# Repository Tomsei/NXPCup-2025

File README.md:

# NXPCup-2025
Software und Hardware für den NXP-Cup 2025
- **Software Ordner:** gesamter erzeugter Quellcode
- **Hardware Ordner:** Dokumentation der gewählten Hardware mitsamt Recherche

# NXP Cup
Der [NXP-Cup](https://nxpcup.nxp.com/) ist ein Internationaler Wettbewerb, ausgerichtet vom Unternehmen NXP.
Es findet jährlich ein Rennen statt, bei dem die Modellfahrzeuge der jeweiligen Teilnehmer gegeneinander antreten. Um zu gewinnen muss das eigene Fahrzeug die unbekannte Rennstrecke in der schnellsten Geschwindigkeit abfahren und zusätzlich noch mit Präzision vor einem Hindernis zum stehen kommen.

# Styleguides
### Code
- Sprache (Variablen, Funktionen): Englisch
- Kommentare: Englisch
- Schreibweise: 
    - CamelCase
    - Funktionen / Variablen: starten klein
    - Typ-Klasse: starten groß
    - Variablen:
        - Boolen: Präfix is (isValid)
        - constant: konsequent großschreiben von CONSTANT
    - Leerzeichen zwischen Operatoren:  
    ```x + y``` anstatt ```a+y```; ```[x, y]``` anstatt ```[x,y]```
    - Klammerung: Klammer in gleicher Zeile dahinter
        ```
        function () {
            ...
        }
        ```
  - #defines werden komplett groß geschrieben ```#define NEW_DEFINE_VALUE```
### GIT
- Commits: Englisch
- Dateien: Englisch ```exmpleFileForDemonstration``` 
    - Der Name von Komponenten wird wenn notwendig mit _KOMPONENTENNAME an Datei angehangen
- Verzeichnisse: Englisch
- Wiki: Deutsch
- Issues: Deutsch

<br>
<br>

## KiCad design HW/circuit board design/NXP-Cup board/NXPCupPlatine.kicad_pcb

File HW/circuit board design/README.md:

# Platinenentwicklung

Hier werden die für die Platinen relevanten Dateien gespeichert. (Gerber sowie Projektdateien und Dokumentation)

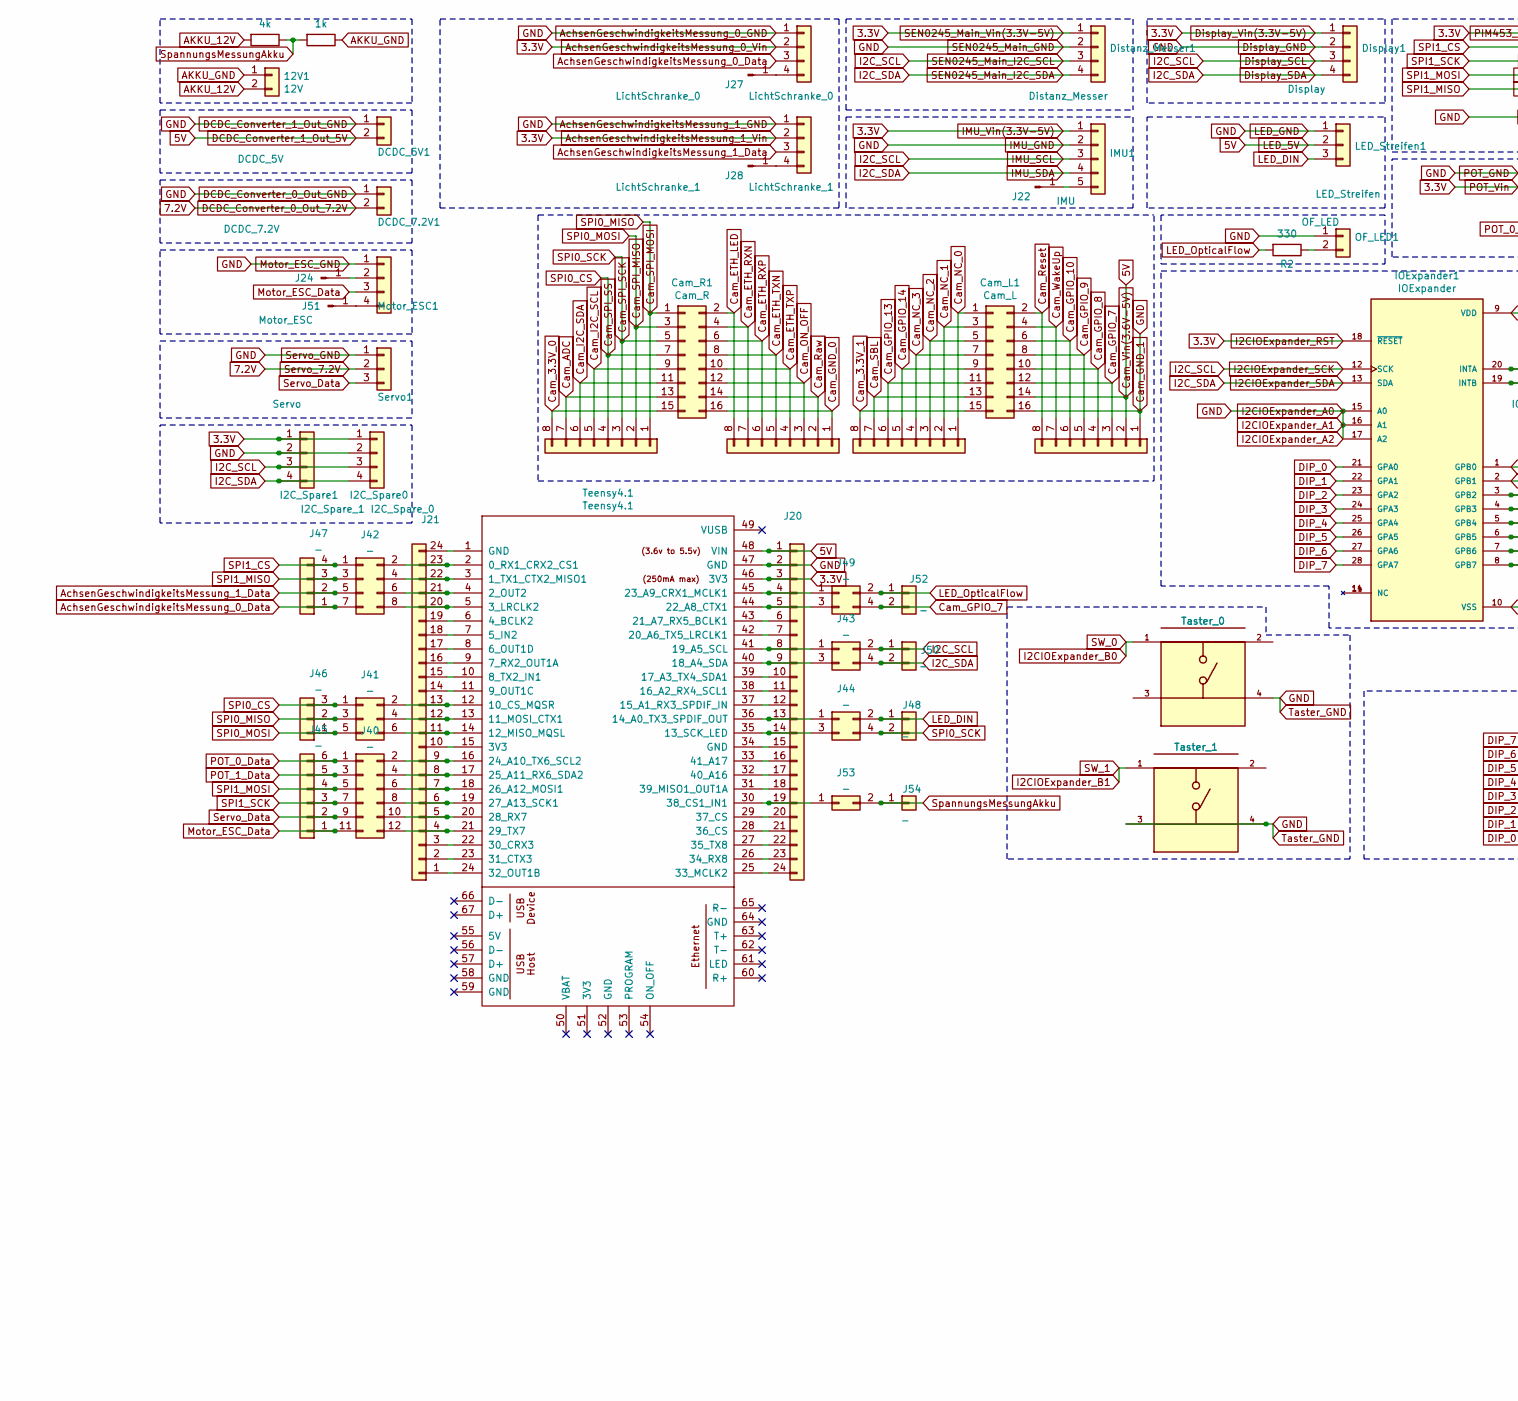
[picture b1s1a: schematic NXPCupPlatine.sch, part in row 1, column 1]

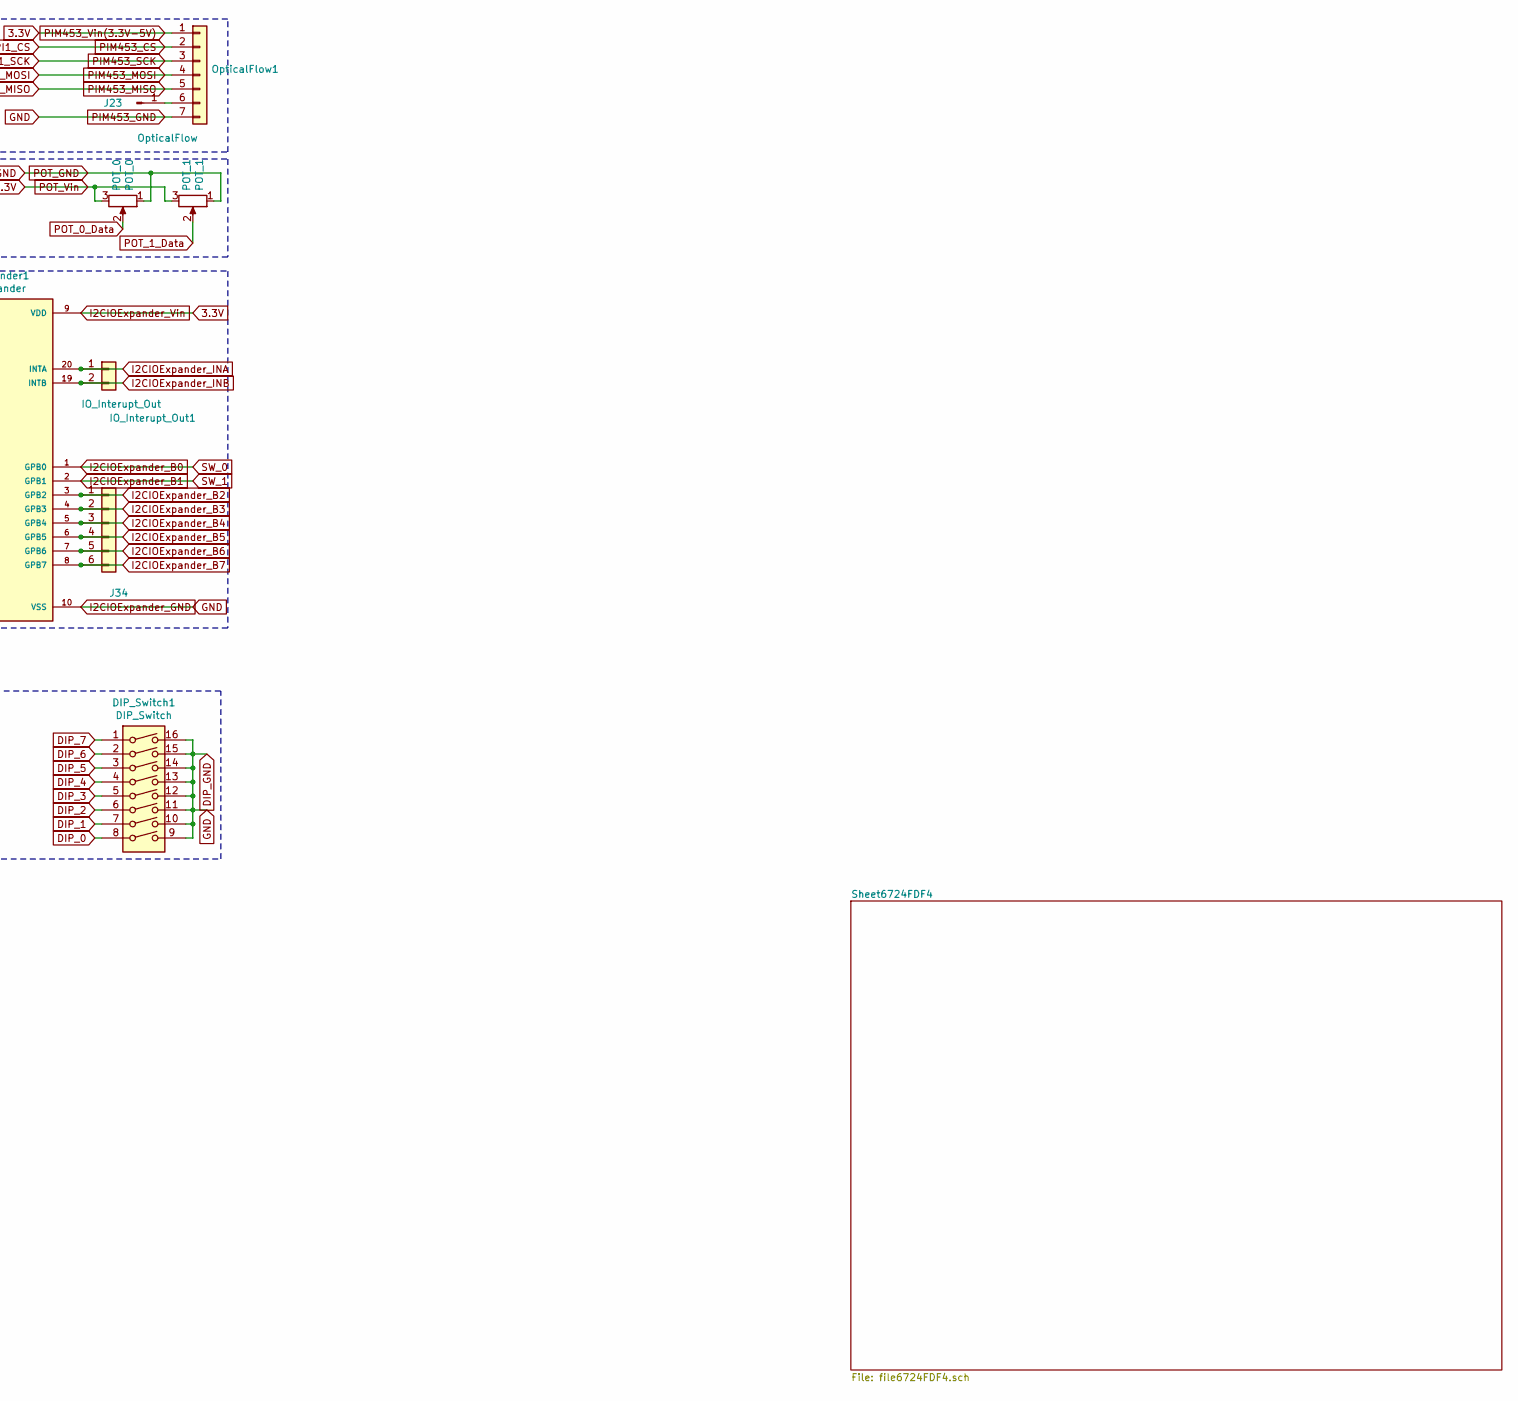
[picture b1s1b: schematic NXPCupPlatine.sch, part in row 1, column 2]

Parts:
12V1: 12V; PinHeader_1x02_P2.54mm_Vertical
Cam_L1: Cam_L; PinHeader_2x08_P2.54mm_Vertical
Cam_R1: Cam_R; PinHeader_2x08_P2.54mm_Vertical
DCDC_5V1: DCDC_5V; PhoenixContact_MSTBA_2,5_2-G_1x02_P5.00mm_Horizontal
DCDC_7.2V1: DCDC_7.2V; PhoenixContact_MSTBA_2,5_2-G_1x02_P5.00mm_Horizontal
DIP_Switch1: DIP_Switch; DIP-16_W7.62mm_LongPads
Display1: Display; PinSocket_1x04_P2.54mm_Vertical
Distanz_Messer1: Distanz_Messer; PinHeader_1x04_P2.54mm_Vertical
I2C_Spare_0: I2C_Spare0; PinHeader_1x04_P2.54mm_Vertical
I2C_Spare_1: I2C_Spare1; PinHeader_1x04_P2.54mm_Vertical
IMU1: IMU; PinHeader_1x05_P2.54mm_Vertical
IOExpander1: IOExpander; DIP787W45P254L3556H508Q28; PARTREV D
IO_Interupt_Out1: IO_Interupt_Out; PinSocket_1x02_P2.54mm_Vertical
J5, J7, J8, J10: PinHeader_1x08_P2.54mm_Vertical
J20, J21: PinHeader_1x24_P2.54mm_Vertical
J22, J23, J24, J27, J28, J51: PinHeader_1x01_P2.54mm_Vertical
J34: PinSocket_1x06_P2.54mm_Vertical
J40: _; PinHeader_2x06_P2.54mm_Vertical
J41: _; PinHeader_2x03_P2.54mm_Vertical
J42: _; PinHeader_2x04_P2.54mm_Vertical
J43, J44, J49: _; PinHeader_2x02_P2.54mm_Vertical
J45: _; PinHeader_1x06_P2.54mm_Vertical
J46: _; PinHeader_1x03_P2.54mm_Vertical
J47: _; PinHeader_1x04_P2.54mm_Vertical
J48, J50, J52: _; PinHeader_1x02_P2.54mm_Vertical
J53: _; PinHeader_2x01_P2.54mm_Vertical
J54: _; PinHeader_1x01_P2.54mm_Vertical
LED_Streifen1: LED_Streifen; PinSocket_1x03_P2.54mm_Vertical
LichtSchranke_0: LichtSchranke_0; PinSocket_1x04_P2.54mm_Vertical
LichtSchranke_1: LichtSchranke_1; PinSocket_1x04_P2.54mm_Vertical
Motor_ESC1: Motor_ESC; PinHeader_1x04_P2.54mm_Vertical
OF_LED1: OF_LED; PinSocket_1x02_P2.54mm_Vertical
OpticalFlow1: OpticalFlow; PinHeader_1x07_P2.54mm_Vertical
POT_0: POT_0; Potentiometer_Alpha_RD901F-40-00D_Single_Vertical
POT_1: POT_1; Potentiometer_Alpha_RD901F-40-00D_Single_Vertical
R0: 4k; R_Axial_DIN0204_L3.6mm_D1.6mm_P1.90mm_Vertical
R1: 1k; R_Axial_DIN0204_L3.6mm_D1.6mm_P1.90mm_Vertical
R2: 330; R_Axial_DIN0204_L3.6mm_D1.6mm_P1.90mm_Vertical
Servo1: Servo; PinHeader_1x03_P2.54mm_Vertical
Taster_0: Taster_0; SW_TS02-66-95-BK-260-LCR-D; PARTREV 1.0
Taster_1: Taster_1; SW_TS02-66-95-BK-260-LCR-D; PARTREV 1.0
Teensy4.1: Teensy4.1; Teensy41

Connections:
3.3V: Display1.1, Distanz_Messer1.1, I2C_Spare_0.1, I2C_Spare_1.1, IMU1.1, IOExpander1.9 (VDD), IOExpander1.18 (~RESET), J20.3, LichtSchranke_0.2, LichtSchranke_1.2, OpticalFlow1.1, POT_0.3, POT_1.3, Teensy4.1.46 (3V3)
5V: Cam_L1.14, DCDC_5V1.2, J10.2, J20.1, LED_Streifen1.2, Teensy4.1.48 (VIN)
7.2V: DCDC_7.2V1.2, Servo1.2
AKKU_12V: 12V1.2, R0.2
AKKU_GND: 12V1.1, R1.1
AchsenGeschwindigkeitsMessung_0_Data: J42.7, J47.1, LichtSchranke_0.3
AchsenGeschwindigkeitsMessung_0_GND: Cam_L1.16, DCDC_5V1.1, DCDC_7.2V1.1, DIP_Switch1.9, DIP_Switch1.10, DIP_Switch1.11, DIP_Switch1.12, DIP_Switch1.13, DIP_Switch1.14, DIP_Switch1.15, DIP_Switch1.16, Display1.2, Distanz_Messer1.2, I2C_Spare_0.2, I2C_Spare_1.2, IMU1.2, IOExpander1.10 (VSS), IOExpander1.15 (A0), IOExpander1.16 (A1), IOExpander1.17 (A2), J10.1, J20.2, LED_Streifen1.1, LichtSchranke_0.1, LichtSchranke_1.1, Motor_ESC1.1, OF_LED1.1, OpticalFlow1.7, POT_0.1, POT_1.1, Servo1.1, Taster_0.4, Taster_1.3, Taster_1.4, Teensy4.1.47 (GND)
AchsenGeschwindigkeitsMessung_1_Data: J42.5, J47.2, LichtSchranke_1.3
Cam_3.3V_0: Cam_R1.15, J5.8
Cam_3.3V_1: Cam_L1.15, J8.8
Cam_ADC: Cam_R1.13, J5.7
Cam_ETH_LED: Cam_R1.2, J7.8
Cam_ETH_RXN: Cam_R1.4, J7.7
Cam_ETH_RXP: Cam_R1.6, J7.6
Cam_ETH_TXN: Cam_R1.8, J7.5
Cam_ETH_TXP: Cam_R1.10, J7.4
Cam_GND_0: Cam_R1.16, J7.1
Cam_GPIO_7: Cam_L1.12, J10.3, J49.4, J52.2
Cam_GPIO_8: Cam_L1.10, J10.4
Cam_GPIO_9: Cam_L1.8, J10.5
Cam_GPIO_10: Cam_L1.6, J10.6
Cam_GPIO_13: Cam_L1.11, J8.6
Cam_GPIO_14: Cam_L1.9, J8.5
Cam_I2C_SCL: Cam_R1.9, J5.5
Cam_I2C_SDA: Cam_R1.11, J5.6
Cam_NC_0: Cam_L1.1, J8.1
Cam_NC_1: Cam_L1.3, J8.2
Cam_NC_2: Cam_L1.5, J8.3
Cam_NC_3: Cam_L1.7, J8.4
Cam_ON_OFF: Cam_R1.12, J7.3
Cam_Raw: Cam_R1.14, J7.2
Cam_Reset: Cam_L1.2, J10.8
Cam_SBL: Cam_L1.13, J8.7
Cam_SPI_MISO: Cam_R1.3, J5.2, J41.5, J46.1
Cam_SPI_MOSI: Cam_R1.1, J5.1, J41.3, J46.2
Cam_SPI_SCK: Cam_R1.5, J5.3, J44.4, J48.2
Cam_SPI_SS: Cam_R1.7, J5.4, J41.1, J46.3
Cam_WakeUp: Cam_L1.4, J10.7
DIP_0: DIP_Switch1.8, IOExpander1.21 (GPA0)
DIP_1: DIP_Switch1.7, IOExpander1.22 (GPA1)
DIP_2: DIP_Switch1.6, IOExpander1.23 (GPA2)
DIP_3: DIP_Switch1.5, IOExpander1.24 (GPA3)
DIP_4: DIP_Switch1.4, IOExpander1.25 (GPA4)
DIP_5: DIP_Switch1.3, IOExpander1.26 (GPA5)
DIP_6: DIP_Switch1.2, IOExpander1.27 (GPA6)
DIP_7: DIP_Switch1.1, IOExpander1.28 (GPA7)
Display_SCL: Display1.3, Distanz_Messer1.3, I2C_Spare_0.3, I2C_Spare_1.3, IMU1.3, IOExpander1.12 (SCK), J43.2, J50.1
Display_SDA: Display1.4, Distanz_Messer1.4, I2C_Spare_0.4, I2C_Spare_1.4, IMU1.4, IOExpander1.13 (SDA), J43.4, J50.2
I2CIOExpander_B0: IOExpander1.1 (GPB0), Taster_0.1
I2CIOExpander_B1: IOExpander1.2 (GPB1), Taster_1.1
I2CIOExpander_B2: IOExpander1.3 (GPB2), J34.1
I2CIOExpander_B3: IOExpander1.4 (GPB3), J34.2
I2CIOExpander_B4: IOExpander1.5 (GPB4), J34.3
I2CIOExpander_B5: IOExpander1.6 (GPB5), J34.4
I2CIOExpander_B6: IOExpander1.7 (GPB6), J34.5
I2CIOExpander_B7: IOExpander1.8 (GPB7), J34.6
I2CIOExpander_INA: IOExpander1.20 (INTA), IO_Interupt_Out1.1
I2CIOExpander_INB: IOExpander1.19 (INTB), IO_Interupt_Out1.2
LED_DIN: J44.2, J48.1, LED_Streifen1.3
LED_OpticalFlow: J49.2, J52.1, R2.2
Motor_ESC_Data: J40.11, J45.1, Motor_ESC1.3
unnamed: IMU1.5, J22.1
unnamed: IOExpander1.11 (NC), IOExpander1.14 (NC)
unnamed: J20.4, J49.1, Teensy4.1.45 (23_A9_CRX1_MCLK1)
unnamed: J20.5, J49.3, Teensy4.1.44 (22_A8_CTX1)
unnamed: J20.6, Teensy4.1.43 (21_A7_RX5_BCLK1)
unnamed: J20.7, Teensy4.1.42 (20_A6_TX5_LRCLK1)
unnamed: J20.8, J43.1, Teensy4.1.41 (19_A5_SCL)
unnamed: J20.9, J43.3, Teensy4.1.40 (18_A4_SDA)
unnamed: J20.10, Teensy4.1.39 (17_A3_TX4_SDA1)
unnamed: J20.11, Teensy4.1.38 (16_A2_RX4_SCL1)
unnamed: J20.12, Teensy4.1.37 (15_A1_RX3_SPDIF_IN)
unnamed: J20.13, J44.1, Teensy4.1.36 (14_A0_TX3_SPDIF_OUT)
unnamed: J20.14, J44.3, Teensy4.1.35 (13_SCK_LED)
unnamed: J20.15, Teensy4.1.34 (GND)
unnamed: J20.16, Teensy4.1.33 (41_A17)
unnamed: J20.17, Teensy4.1.32 (40_A16)
unnamed: J20.18, Teensy4.1.31 (39_MISO1_OUT1A)
unnamed: J20.19, J53.1, Teensy4.1.30 (38_CS1_IN1)
unnamed: J20.20, Teensy4.1.29 (37_CS)
unnamed: J20.21, Teensy4.1.28 (36_CS)
unnamed: J20.22, Teensy4.1.27 (35_TX8)
unnamed: J20.23, Teensy4.1.26 (34_RX8)
unnamed: J20.24, Teensy4.1.25 (33_MCLK2)
unnamed: J21.1, Teensy4.1.24 (32_OUT1B)
unnamed: J21.2, Teensy4.1.23 (31_CTX3)
unnamed: J21.3, Teensy4.1.22 (30_CRX3)
unnamed: J21.4, J40.12, Teensy4.1.21 (29_TX7)
unnamed: J21.5, J40.10, Teensy4.1.20 (28_RX7)
unnamed: J21.6, J40.8, Teensy4.1.19 (27_A13_SCK1)
unnamed: J21.7, J40.6, Teensy4.1.18 (26_A12_MOSI1)
unnamed: J21.8, J40.4, Teensy4.1.17 (25_A11_RX6_SDA2)
unnamed: J21.9, J40.2, Teensy4.1.16 (24_A10_TX6_SCL2)
unnamed: J21.10, Teensy4.1.15 (3V3)
unnamed: J21.11, J41.6, Teensy4.1.14 (12_MISO_MQSL)
unnamed: J21.12, J41.4, Teensy4.1.13 (11_MOSI_CTX1)
unnamed: J21.13, J41.2, Teensy4.1.12 (10_CS_MQSR)
unnamed: J21.14, Teensy4.1.11 (9_OUT1C)
unnamed: J21.15, Teensy4.1.10 (8_TX2_IN1)
unnamed: J21.16, Teensy4.1.9 (7_RX2_OUT1A)
unnamed: J21.17, Teensy4.1.8 (6_OUT1D)
unnamed: J21.18, Teensy4.1.7 (5_IN2)
unnamed: J21.19, Teensy4.1.6 (4_BCLK2)
unnamed: J21.20, J42.8, Teensy4.1.5 (3_LRCLK2)
unnamed: J21.21, J42.6, Teensy4.1.4 (2_OUT2)
unnamed: J21.22, J42.4, Teensy4.1.3 (1_TX1_CTX2_MISO1)
unnamed: J21.23, J42.2, Teensy4.1.2 (0_RX1_CRX2_CS1)
unnamed: J21.24, Teensy4.1.1 (GND)
unnamed: J23.1, OpticalFlow1.6
unnamed: J24.1, Motor_ESC1.2
unnamed: J27.1, LichtSchranke_0.4
unnamed: J28.1, LichtSchranke_1.4
unnamed: J51.1, Motor_ESC1.4
unnamed: OF_LED1.2, R2.1
PIM453_CS: J42.1, J47.4, OpticalFlow1.2
PIM453_MISO: J42.3, J47.3, OpticalFlow1.5
PIM453_MOSI: J40.5, J45.4, OpticalFlow1.4
PIM453_SCK: J40.7, J45.3, OpticalFlow1.3
POT_0_Data: J40.1, J45.6, POT_0.2
POT_1_Data: J40.3, J45.5, POT_1.2
Servo_Data: J40.9, J45.2, Servo1.3
SpannungsMessungAkku: J53.2, J54.1, R0.1, R1.2

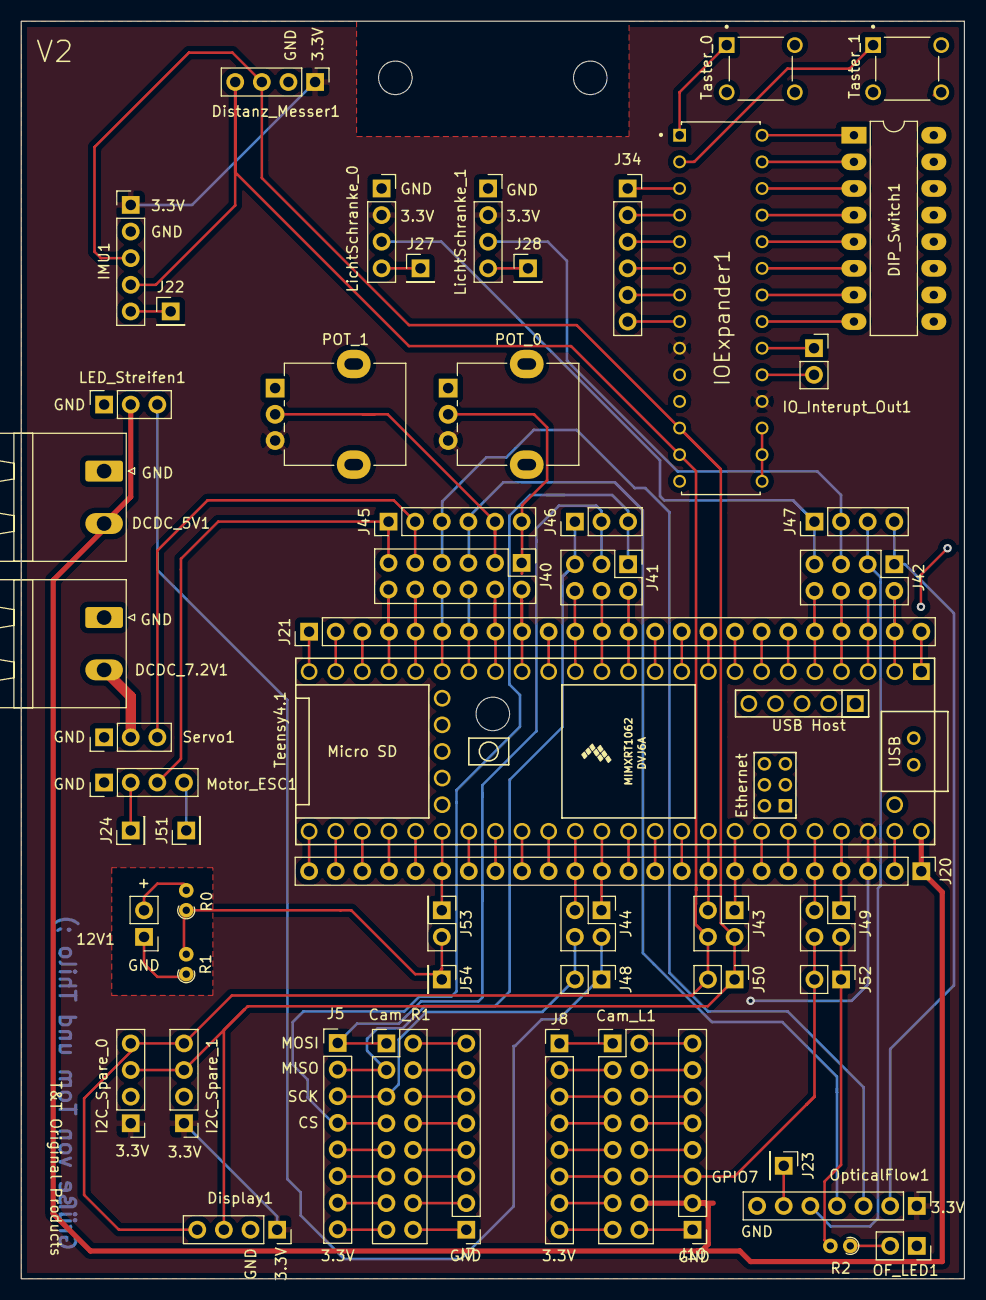
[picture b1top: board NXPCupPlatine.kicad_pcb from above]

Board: 2 copper layers, 90.0 x 120.0 mm, 55 parts (0 on the bottom side), 122 nets.

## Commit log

2024-07-11 initial structure
2024-07-18 add research structure
2024-07-18 complete research strucutre
2024-07-18 add more research results
2024-07-18 add first research results
2024-07-19 add styleguide
2024-07-21 add research results from 17.07
2024-07-23 add research results distance measurement
2024-07-23 add more research (distance measurement)
2024-07-23 add new research results
2024-07-24 add usecase + functional requirements
2024-07-25 rename directorys
2024-07-29 add some camera research
2024-08-01 some more research
2024-08-12 add new research (camera, display...)
2024-08-13 more processor research
2024-08-15 add processor resarch of (14.08)
2024-08-15 general structure
2024-08-16 clean up of research files
2024-08-16 update mikrocontroller research
2024-08-17 start defining Hardware-Kit (Teensy + Cam)
2024-08-19 add research results of 17.08
2024-08-19 add research results NXP-Gitbook
2024-08-20 new research (camera, car racing kit)
2024-08-21 first kit design
2024-08-21 add some changes to first kit
2024-08-24 update research results for kit
2024-08-26 update research (motor links)
2024-08-27 add servo research
2024-08-29 clean up research
2024-09-18 Remove research of file dir; Add HW dir structure
2024-09-18 initiate project with blink on teensy
2024-09-18 rename to PlatformIO
2024-09-23 component test optical flow
2024-09-23 component test ToF distance measurement
2024-09-23 component test ARD Linefinder
2024-09-23 rework single component tests
2024-09-24 component test servo (not testet!)
2024-09-24 component test motor (not testet!)
2024-09-24 component test IMU (not testst!)
2024-09-30 update files for complete component test
2024-09-30 start test for cam spi to teensy
2024-10-03 fix driving car
2024-10-03 add spi test script for single data transfer
2024-10-03 rename spi test scritps
2024-10-03 rename folder
2024-10-03 add first wifi test
2024-10-17 add examples for wifi control of OpenMV Cam
2024-10-17 add Example for Accespoint Asynccontrol of the camera
2024-10-17 change param name
2024-10-28 update pin config for new circuit Board
2024-10-30 motor tests
2024-10-30 preperation for spi
2024-10-30 add spi examplescript (Cam)
2024-10-30 working teensy spi slave
2024-10-30 remove spi single byte test
2024-10-30 add example: controle car engie via wifi
2024-11-04 component test display (add library)
2024-11-04 change to Adafruit Display library
2024-11-04 test display while driving
2024-11-06 structure adafruit basic libs and add license
2024-11-06 add IO Expander lib (source code and license)
2024-11-06 add IO Expander
2024-11-06 add poti
2024-11-06 clean up programm
2024-11-06 rename dir of Adafruit_Bus_IO library
2024-11-06 structure display libs and add license
2024-11-07 update imu lib and add license
2024-11-07 rename dir
2024-11-07 rename Opticalflow dir and add license
2024-11-07 rename Tof dir and add license
2024-11-07 cleanup single components cam, display, imu, io-expander
2024-11-07 clean up single components motor, servo, poti, ToF, IR - add readme
2024-11-07 clean up main
2024-11-07 more main clean up :)
2024-11-07 rename pin defines
2024-11-21 add example SPI Write Lines
2024-11-21 fix IO Expander warning
2024-11-21 clean up single components
2024-11-21 first attempt of camera analysis
2024-11-21 print of the img and img lines via cameraAnalysis
2024-11-21 fix spi transfer of gray image + add pixelprint method (open MV Cam)
2024-11-21 add sobel calculation
2024-11-22 add basic implementation of calculate track center
2024-11-22 basic driving test - no structure! need to be changed!
2024-12-10 rework single components - namespace
2024-12-10 add led Strip
2024-12-10 fixes to compile - currently dont driving
2024-12-11 fixes so car can drive like before
2024-12-11 start structure concept
2024-12-11 possible structure without class
2024-12-11 add concept with static classes for Data visualisation
2024-12-11 start with boardInput Control
2024-12-19 add implementation to board Input Control for setup, update, ...
2024-12-19 more data Visualisation (setup, set Led Color....)
2024-12-19 start structure of DataVis and Board Input working
2024-12-27 comment board input + tenary Operation (engineEnabled)
2025-01-02 change showNumber to show correct number
2025-01-02 start structure for driving control (servo, esc)
2025-01-02 Update Board Input for use of single Dipswitsch State
2025-01-02 start sensor structre (ToF distance)
2025-01-02 update DipSwitch single Value
2025-01-02 add servo enable control
2025-01-02 correct steering control
2025-01-02 structure optical flow
2025-01-02 add imu sensor
2025-01-02 identify servo bug (led problem - no solution)
2025-01-03 add linFinder code
    hw integration is needed!
2025-01-03 rename cameraAnalysis
2025-01-03 rename 2
2025-01-03 structure test while driving
2025-01-03 clean up a few things
2025-01-04 rework to structure with namespaces
2025-01-04 structure rework woriking
2025-01-04 complete driving test
2025-01-13 start reworking camera structure
2025-01-13 try swapped buffer
2025-01-13 clean Up cameraAnalysis
2025-01-13 cleanup camera files
2025-01-13 rename camera file
2025-01-17 change the led library to FastLed
2025-01-17 Update Single Components to new LED Library
2025-01-17 Update README.md
    Link Fas LED
2025-01-17 update camera code of single Component
2025-01-17 Licens and readme for SPI Slave lib
2025-01-17 comment boardInput
2025-01-17 comment gloabelConfig
2025-01-17 comment data Visualisation
2025-01-18 comment display
2025-01-18 comment ledstrip
2025-01-18 comment driving control
2025-01-18 comment engine
2025-01-18 comment servo
2025-01-18 comment imu and use motionData Struct
2025-01-18 add library references
2025-01-18 comment linefinder
2025-01-18 comment optical flow
2025-01-18 comment tof Distance
2025-01-18 comment sensor
2025-01-18 comment single components
2025-01-18 correct some comments
2025-01-20 working test imu data struct
2025-01-21 add Library Links to Readme files
2025-01-21 decrease fastLED lib
2025-01-22 add carLogic for car Control
2025-01-22 change steering and engine enabled
2025-01-23 stable driving
2025-01-23 add wall stop
2025-01-23 test optical Flow values
2025-01-29 driving faster than before - servo and camera analysis changes
2025-01-30 working - time Measurement 30.01.2025
2025-02-13 Basic Speed changes + integration of Bluetooth module
2025-02-18 try interupt for Line finder
2025-02-18 start witch openMV Firmwaretests
2025-02-18 change sleep time (SPI) + some tests
2025-02-18 driving fast
2025-02-18 driving faster
2025-02-20 take time 20.02
2025-02-20 update straight
2025-02-21 error handling (try to figure out why teensy stop)
2025-02-27 add firmware test Code
2025-02-27 driving test 27.02.2025
2025-03-01 spi tests on firmware
2025-03-01 more firmware improvment
2025-03-05 clean up boardInput, configuration, datavisualisation
2025-03-05 add #ifdef to CONSOLE
2025-03-05 clean up driving Control
2025-03-05 clean up sensors
2025-03-05 split Cameraanalysis in multiple files
2025-03-05 start cleanup camera
2025-03-05 rework camera swap buffer - driving
2025-03-05 clean up image analysis
2025-03-05 update comment image Analysis
2025-03-05 clean up row analysis
2025-03-05 cleanup firmware analysis and debug template function
2025-03-05 add firmware improvements
2025-03-05 prepare new files for new firmware
2025-03-06 prepare teensy for analyse on camera
2025-03-06 more analyse stuff on teensy
2025-03-07 driving test with new camera Analysis
2025-03-07 speed test
2025-03-07 saving camera video on sd card
2025-03-07 video Testing camera analysis
2025-03-07 add new implementation of ard line finder
2025-03-08 running system with new firmware version (video + streaming possible)
2025-03-08 cleanup acces point example scripts
2025-03-08 updating single component to new software
2025-03-08 clean up camera scripts finished
2025-03-08 update firmware comments
2025-03-11 start implementation for timing control
2025-03-12 board input data public
2025-03-13 some test
2025-03-14 firmware changes to detect if track centers is not on track anymore
2025-03-14 Single Component Test - remove inlcude error
2025-03-14 clean up single component servo
2025-03-15 add comments to SPI-Slave lib
2025-03-19 driving test of 18.03.2025
2025-03-19 inlcude timed Tasks vor leds and speed + add display visualisation
2025-03-19 prepare moving #defines
2025-03-20 Test Commit
2025-03-20 woriking speed measurement
2025-03-21 add bluetooth and speed Control
2025-03-22 change config files
2025-03-22 rename visualization
2025-03-25 trying some firmware stuff
2025-03-26 Interim status of clean-up
2025-03-26 cleanup and update firmware module
2025-03-26 clean up teensy spi
2025-03-26 bugfix for trackCenter[1] byte
2025-03-26 working cleanup
2025-03-26 change finishLineDetection
2025-03-26 try steering optimation (with far line ahead)
2025-03-27 update to new sensor
2025-03-27 add config to disable finishLineDetection
2025-03-27 skip frames if nothing to see
2025-03-27 firmware update (min edge Width)
2025-03-27 firmware test
2025-03-31 fast test from 28.02.
2025-03-31 update firmware module (fix finishline but) + fix steering Offset left
2025-03-31 improve finish line detection
2025-03-31 update scan offset
2025-04-01 remove error check in main
2025-04-01 switch dip-switsch to Teensy pins
2025-04-01 drive withoud io-expander
2025-04-01 enable control of cutting curves
2025-04-01 add firmware visualisation of steering lines
2025-04-01 firmware changes (crossing)
2025-04-01 finischline detection test + configure cutting curves + change Tof i2c
2025-04-01 min cross detection line firmware
2025-04-01 try to fix tof bug - better driving (request tof just if finish found
2025-04-02 try to improve cross detection
2025-04-02 fix new cross test
2025-04-02 optimize slow driving after finish line detection
2025-04-03 show setup done display
2025-04-03 Add speed configuration via dip switch
2025-04-09 Auto stash before merge of "main" and "origin/main"
2025-04-10 start with clean up
2025-04-10 add board design documentation
2025-04-10 add 3d models
2025-04-10 rename optical flow 3d model
2025-04-10 definition of software kit
2025-04-10 remove spelling mistake
2025-04-10 include config to servo
2025-04-10 rename firmwareAnalysis
2025-04-10 add link to WiFi to tutorial
2025-04-10 comment configuration files
2025-04-11 clean up SW-Kit
2025-04-11 start cleanup
2025-04-11 clean up transfer Image Lines
2025-04-11 clean up analysis on teensy
2025-04-11 renam ANALYSIS_ON_CAMERA
2025-04-11 Software-Kit
2025-04-11 hardware files
2025-04-11 update READ
2025-04-11 clean up configurations
2025-04-11 rename firmware Analysis
2025-04-11 update cam scripts
2025-04-11 clean up board input
2025-04-11 clean up row + image analysis
2025-04-11 clean up teensy lib
2025-04-11 clean up trackCenterAnalysis
2025-04-11 clean up data visualization
2025-04-11 clean up car logic
2025-04-11 remove not needed firmware
2025-04-11 clean up timing control
2025-04-11 fix configuration include
2025-05-09 working break tests
2025-05-09 prepare configuration
